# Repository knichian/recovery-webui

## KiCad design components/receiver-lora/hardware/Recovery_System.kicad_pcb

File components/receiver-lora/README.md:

# Receiver LoRa

Receiver de solo do sistema de recuperação da Serra Rocketry. Recebe telemetria
via LoRa (915 MHz) do satellite (#213) e dos foguetes (#11/#51), preenche
hora/data com GPS local e retransmite pela Serial (USB) no formato do protocolo
Recovery WebUI. Também é o nó central do mesh de trilateração por RSSI.

> Documentação técnica completa (arquitetura, protocolos, ADRs, simulação de
> precisão): [docs/firmware.md](docs/firmware.md)

## Hardware

| Item        | Descrição                                    |
|-------------|----------------------------------------------|
| MCU         | ESP32 DevKit V1 (DOIT)                       |
| Rádio       | RFM95W (LoRa 915 MHz, SPI)                   |
| GPS         | NEO-8M (UART2)                               |
| Antena      | Yagi 3–5 elementos, 915 MHz (ver firmware.md)|

**Atenção**: o módulo LoRa opera estritamente em 3.3 V — nunca ligue VCC no 5V.

### Pinagem

| Pino | Função    | Componente      |
|------|-----------|-----------------|
| 18   | SPI SCK   | RFM95W SCK      |
| 23   | SPI MOSI  | RFM95W MOSI     |
| 19   | SPI MISO  | RFM95W MISO     |
| 5    | SPI CS    | RFM95W NSS/CS   |
| 14   | LoRa RST  | RFM95W RESET    |
| 2    | LoRa IRQ  | RFM95W DIO0     |
| 16   | UART2 RX  | GPS TX          |
| 17   | UART2 TX  | GPS RX          |

## Requisitos

- [PlatformIO Core](https://docs.platformio.org/en/latest/core/index.html)
  (CLI) ou a extensão PlatformIO no VS Code. Instalação via pip/pyenv:

  ```bash
  pip install -U platformio
  ```

- Cabo USB (o DevKit V1 usa chip USB-UART; porte USB nativo não é usado)

## Build

```bash
cd components/receiver-lora/firmware

# Compilar (env:esp32doit-devkit-v1)
pio run
```

## Upload

```bash
# Porta tipica no Linux: /dev/ttyUSB0 (ou /dev/ttyUSB1)
pio run -t upload --upload-port /dev/ttyUSB0
```

Se a porta estiver ocupada por um monitor serial, feche-o antes. Se o upload
falhar em `Connecting........_____`, segure o botão **BOOT** da placa durante
a conexão (raro; geralmente necessário só na primeira gravação ou após um
firmware que travou o UART).

## Monitor serial

```bash
pio device monitor -b 115200
```

Saída esperada no boot:

```
[GPS] aguardando fix...
[LoRa] RX iniciado em 915 MHz
[LoRa] RX (RSSI=-67): #213,1205,42,...
[MESH] Beacons ativos: 3/3 | ouvindo o satellite: 3 | ultimo pkt: #4521
```

Logs de diagnóstico: `[LOST]` (pacotes perdidos), `[STATS]` (taxa de perda e
erros de parse), `[MESH]` (saúde do mesh de beacons), `[TRI]` (correção de
trilateração aplicada).

## Testar

### 1. Teste em banco (sem rádio)

1. Conecte a placa via USB e abra o monitor serial (`pio device monitor -b 115200`).
2. Verifique no boot que não há mensagens de erro de inicialização.
3. Se o GPS estiver conectado, aguarde fix ao céu aberto (1–5 min no primeiro
   ligamento, depois segundos). Sem GPS conectado o firmware segue operando —
   os campos `hora`/`data` saem como 0.

### 2. Teste de recepção LoRa (loopback/ponto a ponto)

1. Monte o circuito da pinagem acima e verifique a antena no RFM95W **antes de
   energizar** (transmitir sem antena danifica o PA).
2. Use um segundo dispositivo (beacon ou satellite de bancada) configurado com
   os **mesmos parâmetros de rádio** — eles devem bater com o transmissor real:
   frequência 915 MHz, sync word `0xF3`, SF7, BW 125 kHz, CR 4/5
   (`include/config.h`).
3. Transmissor de bancada enviando o formato `#213,...#` (18 campos) deve
   produzir no monitor:

   ```
   [LoRa] RX (RSSI=-67): #213,1205,42,150.50,25.30,45.20,...
   ```

4. Pausar o transmissor e retomar com `count` adiantado valida o detector de
   pacotes perdidos:

   ```
   [LOST] 3 pacote(s) perdido(s) — count 45 -> 49 | total perdidos: 3
   ```

### 3. Teste do mesh de trilateração

1. Ligue pelo menos 2 beacons além do receiver (mínimo de
   `TRILAT_MIN_LISTENERS = 3` ouvintes), todos com GPS fix e ouvindo o mesmo
   satellite.
2. O cesto fecha e o receiver emite o `#213` com lat/lon corrigida:

   ```
   [TRI] pkt#4523 corrigido: -21.775551,-48.175565 | ouvintes=4 | residuo=112.3m
   ```

3. Sem beacons suficientes, o pacote sai com o GPS cru do satellite após a
   janela de 900 ms (`TRILAT_BASKET_WAIT_MS`) — comportamento de fallback
   esperado.
4. Resíduo > 1500 m (`TRILAT_MAX_RESIDUAL_M`) também cai no GPS cru (solução
   LSQ descartada).

### 4. Teste de integração com o Recovery WebUI

1. Conecte o receiver à máquina que roda a WebUI e identifique a porta:

   ```bash
   ls /dev/ttyUSB*
   ```

2. Aponte a WebUI para a porta serial — o receiver emite o formato v2.0
   (24 campos, `TEAM_ID,millis,...,rssi`) pela Serial a cada pacote recebido.
3. Valide na interface que os pacotes aparecem com hora/data preenchidas pelo
   GPS local do receiver.

## Configuração rápida (`include/config.h`)

| Parâmetro            | Default | Descrição                                  |
|----------------------|---------|--------------------------------------------|
| `LORA_FREQUENCY`     | 915E6   | Frequência em Hz (915 MHz Brasil)          |
| `LORA_SYNC_WORD`     | 0xF3    | Deve bater com o transmissor               |
| `TRILAT_MIN_LISTENERS`| 3      | Ouvintes mínimos p/ fechar o cesto         |
| `TRILAT_TX_POWER_DBM`| 20      | Potência TX do satellite (link budget RSSI)|

A lista completa de parâmetros de trilateração está em
[docs/firmware.md](docs/firmware.md#trilateracao--parametros-configh).

## Estrutura do projeto

```
firmware/
├── platformio.ini          — Config do PlatformIO (env, libs, flags)
├── partitions.csv          — Tabela de partições
├── include/                — config.h e headers
├── src/                    — main.cpp, LoraReceiver, GpsModule, Trilateration
└── lib/                    — Bibliotecas locais (se houver)
```

Dependências gerenciadas pelo PlatformIO (instaladas automaticamente no build):

- `sandeepmistry/LoRa @ ^0.8.0`
- `mikalhart/TinyGPSPlus @ ^1.0.3`

## Solução de problemas

| Sintoma | Causa provável / correção |
|---------|---------------------------|
| `LoRa init failed` | Fiação divergente do `config.h`, falta de antena, módulo alimentado em 5V |
| RSSI sempre -127 / nada recebido | Sync word ou frequência diferentes do transmissor; antena desconectada |
| Upload trava em `Connecting...` | Feche o monitor serial; segure BOOT durante o connect |
| Porta não aparece | Instale o driver CP210x/CH340 conforme o chip USB-UART da sua placa |
| Hora/data = 0 | GPS sem fix — leve ao céu aberto e aguarde |

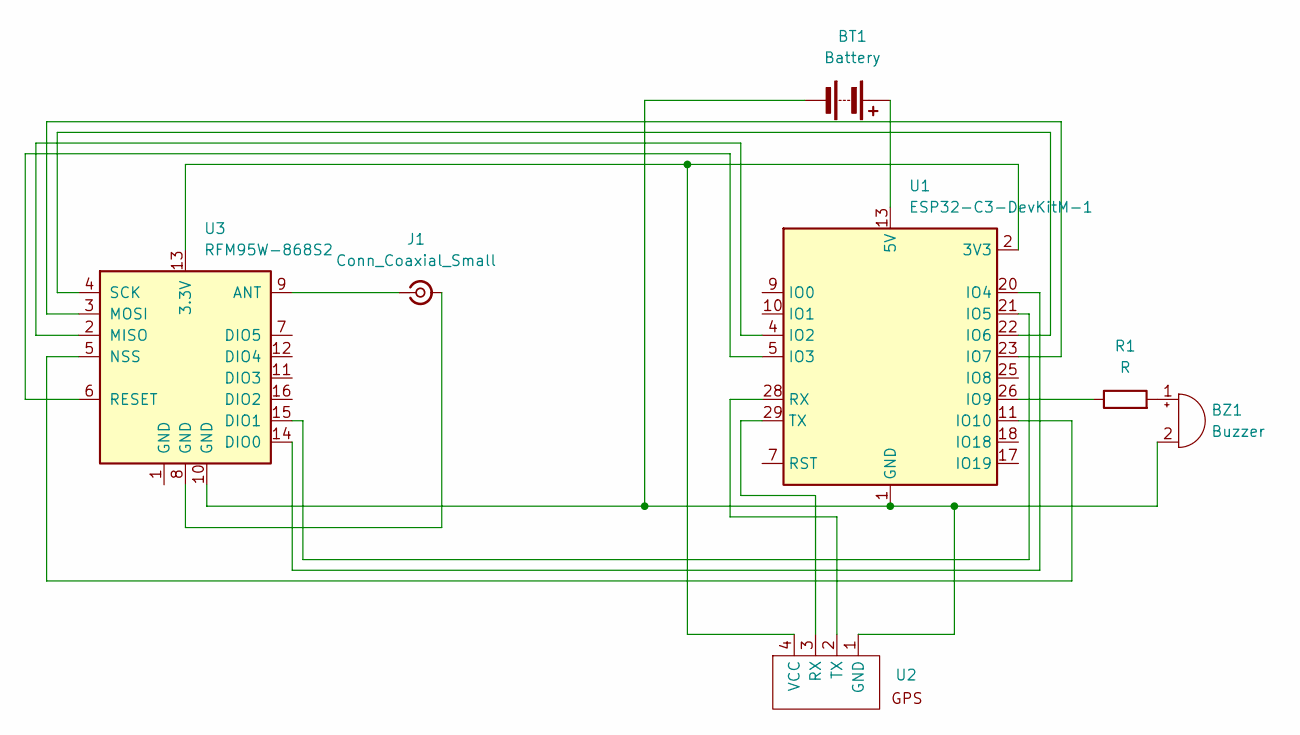
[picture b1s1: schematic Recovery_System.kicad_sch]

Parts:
BT1: Battery; JST_PH_B2B-PH-K_1x02_P2.00mm_Vertical
BZ1: Buzzer; Buzzer_TDK_PS1240P02BT_D12.2mm_H6.5mm
J1: Conn_Coaxial_Small; SMA_Amphenol_901-144_Vertical
R1: R; R_Axial_DIN0204_L3.6mm_D1.6mm_P5.08mm_Horizontal
U1: ESP32-C3-DevKitM-1
U2: GPS
U3: RFM95W-868S2; HOPERF_RFM9XW_SMD

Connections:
unnamed: BT1.1 (+), U1.13 (5V), U1.14 (5V)
unnamed: BT1.2 (-), BZ1.2 (-), U1.1 (GND), U1.6 (GND), U1.8 (GND), U1.12 (GND), U1.15 (GND), U1.16 (GND), U1.19 (GND), U1.24 (GND), U1.27 (GND), U1.30 (GND), U2.1 (GND), U3.10 (GND)
unnamed: BZ1.1 (+), R1.2
unnamed: J1.2 (Ext), U3.8 (GND)
unnamed: J1.1 (In), U3.9 (ANT)
unnamed: U1.4 (IO2), U3.2 (MISO)
unnamed: U1.5 (IO3), U3.6 (RESET)
unnamed: U1.20 (IO4), U3.14 (DIO0)
unnamed: U1.21 (IO5), U3.15 (DIO1)
unnamed: U1.22 (IO6), U3.4 (SCK)
unnamed: U1.23 (IO7), U3.3 (MOSI)
unnamed: R1.1, U1.26 (IO9)
unnamed: U1.11 (IO10), U3.5 (NSS)
unnamed: U1.28 (RX), U2.2 (TX)
unnamed: U1.29 (TX), U2.3 (RX)
unnamed: U1.2 (3V3), U1.3 (3V3), U2.4 (VCC), U3.13 (3.3V)

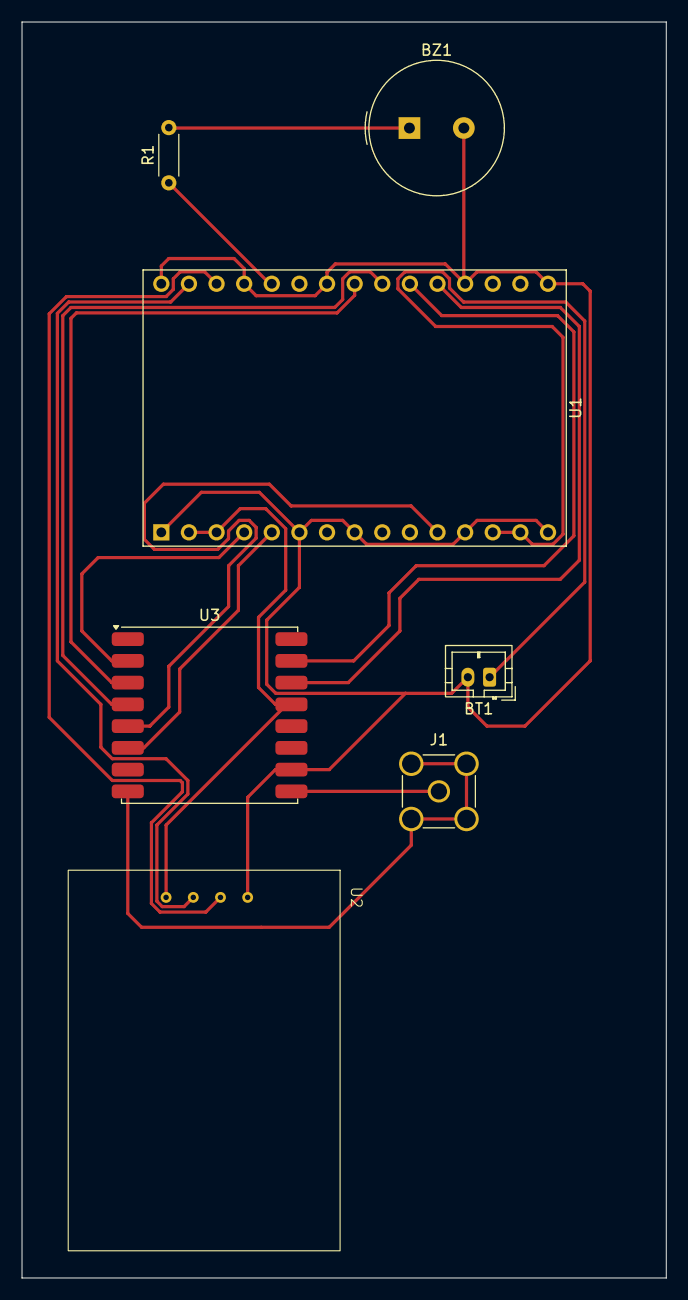
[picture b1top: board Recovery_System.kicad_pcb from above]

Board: 2 copper layers, 59.2 x 115.5 mm, 7 parts (0 on the bottom side), 16 nets.

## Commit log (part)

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2026-05-21 fix: omitindo __pycache__ com .gitignore
2026-05-28 feat[flask]: adicionando novo sistema de logging
2026-05-28 feat[flask]: criando persistencia de reescanear portas seriais
2026-05-28 fix[flask]: mudando a formatação do logging para conter segundos
2026-06-01 checkpoint[quicksave]
